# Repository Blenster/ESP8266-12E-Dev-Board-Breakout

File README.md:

# ESP8266-12E-Dev-Board-Breakout
KiCAD project to create a simple breakout PCB for use with various ESP8266-12E dev boards.

Designed around this pinout: https://m.media-amazon.com/images/I/812vnqUs5tL._AC_SL1500_.jpg

PCB has a few sample LEDs and parts in both through hole and surface mount configurations. The LEDs are on PWM capable pins and the inputs are on non-PWM pins. The circuit is an example circuit and should not be used as it currently is; this is merely a demonstration project to give a good starting point.

NOTE: this is based on a 5V DC project and a TODO item is to change this to 3.3 values.

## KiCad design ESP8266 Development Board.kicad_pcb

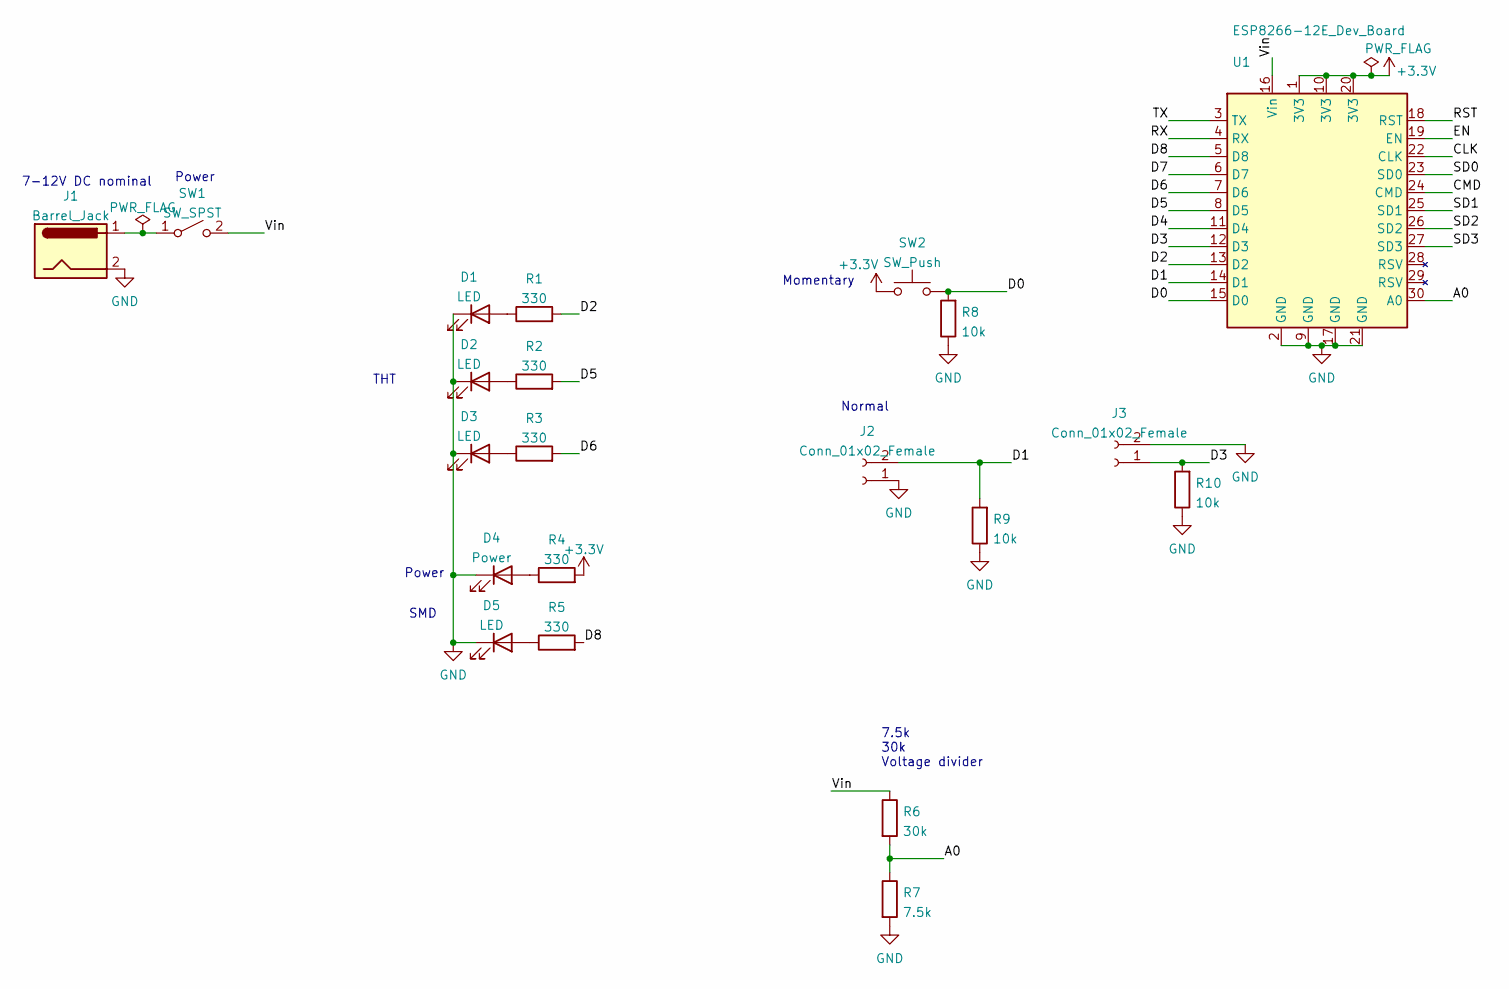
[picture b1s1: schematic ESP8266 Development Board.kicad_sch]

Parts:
D1, D2, D3: LED; LED_D5.0mm
D4: Power; LED_0805_2012Metric
D5: LED; LED_0805_2012Metric
J1: Barrel_Jack; BarrelJack_CUI_PJ-063AH_Horizontal
J2, J3: Conn_01x02_Female; JST_EH_B2B-EH-A_1x02_P2.50mm_Vertical
R1, R2, R3: 330; R_Axial_DIN0207_L6.3mm_D2.5mm_P10.16mm_Horizontal
R4, R5: 330; R_0805_2012Metric
R6: 30k; R_0805_2012Metric
R7: 7.5k; R_0805_2012Metric
R8, R9, R10: 10k; R_0805_2012Metric
SW1: SW_SPST; SW_Tactile_SPST_Angled_PTS645Vx58-2LFS
SW2: SW_Push; SW_PUSH_6mm
U1: ESP8266-12E_Dev_Board; ESP8266-12E

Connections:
+3V3: R4.2, SW2.1, U1.1 (3V3), U1.10 (3V3), U1.20 (3V3)
/A0: R6.2, R7.1, U1.30 (A0)
/CLK: U1.22 (CLK)
/CMD: U1.24 (CMD)
/D0: R8.2, SW2.2, U1.15 (D0)
/D1: J2.2, R9.2, U1.14 (D1)
/D2: R1.2, U1.13 (D2)
/D3: J3.1, R10.2, U1.12 (D3)
/D4: U1.11 (D4)
/D5: R2.2, U1.8 (D5)
/D6: R3.2, U1.7 (D6)
/D7: U1.6 (D7)
/D8: R5.2, U1.5 (D8)
/EN: U1.19 (EN)
/RST: U1.18 (RST)
/RX: U1.4 (RX)
/SD0: U1.23 (SD0)
/SD1: U1.25 (SD1)
/SD2: U1.26 (SD2)
/SD3: U1.27 (SD3)
/TX: U1.3 (TX)
/Vin: R6.1, SW1.2 (B), U1.16 (Vin)
GND: D1.1 (K), D2.1 (K), D3.1 (K), D4.1 (K), D5.1 (K), J1.2, J2.1, J3.2, R7.2, R8.1, R9.1, R10.1, U1.2 (GND), U1.9 (GND), U1.17 (GND), U1.21 (GND)
unnamed: D1.2 (A), R1.1
unnamed: D2.2 (A), R2.1
unnamed: D3.2 (A), R3.1
unnamed: D4.2 (A), R4.1
unnamed: D5.2 (A), R5.1
unnamed: J1.1, SW1.1 (A)

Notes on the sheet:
7.5k 30k Voltage divider
Power
THT
Normal
SMD
7-12V DC nominal
Momentary

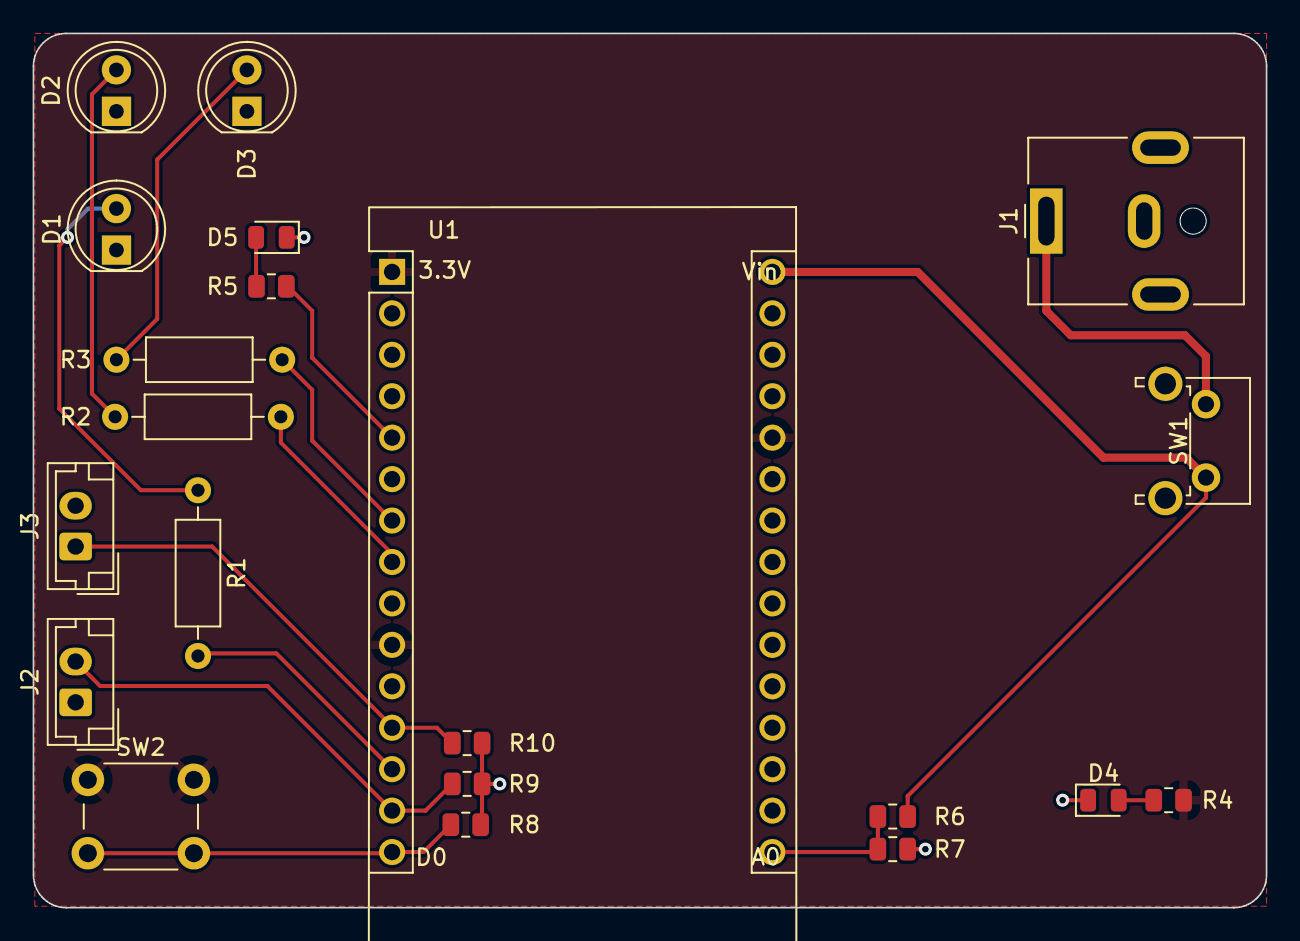
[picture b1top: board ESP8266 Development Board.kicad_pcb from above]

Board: 2 copper layers, 75.6 x 53.6 mm, 21 parts (0 on the bottom side), 17 nets.

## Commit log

2022-02-06 Initial Commit
    NOTE: This initial commit HAS NOT BEEN TESTED; future tweaks will occur after I've had a chance to try this out.
2022-02-06 Initial edit
    I need to do a lot more work here. Give me some time.
2022-02-06 Initial commit
    Custom footprint for the board (NOTE: not yet tested)
2022-02-09 Updated footprint to better guess; STILL NOT VERIFIED
    Got a picture with some measurements and updated the ESP8266-12E footprint.
2022-02-09 Updated to reduce width from my guess to measurements provided by Lockadoc
    Got a picture with some measurements and updated the ESP8266-12E footprint.
2022-02-11 Added JST headers
    Added JST headers with ground points and cool 3D models
